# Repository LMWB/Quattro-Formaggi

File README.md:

# DS18B20_OneWire
One Wire Temperature Sensor Breakout Board on Arduino Shield Format and STM32 Nucleo-F446 Based Software

# Features
- four channels 1-Wire Interface with onboard driver stage 
- designed for DS18B20 Temperature Sensor but any 1-Wire Sensor / Actor would do (minor software adjustments required)
- Industrial ready CAN-Bus interface
    - works with standard (11-Bit) and extended (29-Bit) CAN identifier
- Industrial ready Modbus interface will come soon
- Arduino-Shield layout will fit on several Dev-Boards including all Nucleo-64 boards and Arduino-UNO boards

The 1-Wire Search Algorithm and Driver Stage are basically taken from MAXIM Datasheet and Microship App-Notes.

To study some of my testing done so far please have a look [here](/Testing/README.md).

# Quattro Formaggi vs. Quattro Stagioni

# ToDo
- add User-LED on Arduino Shield (Nucleo LED is covered) [HW]
- add Temperature Results to CAN Message [SW]
- use bigger terminal blocks for 1-Wire Interface [HW]
- use bigger terminal blocks for Power Supply and CAN [HW]

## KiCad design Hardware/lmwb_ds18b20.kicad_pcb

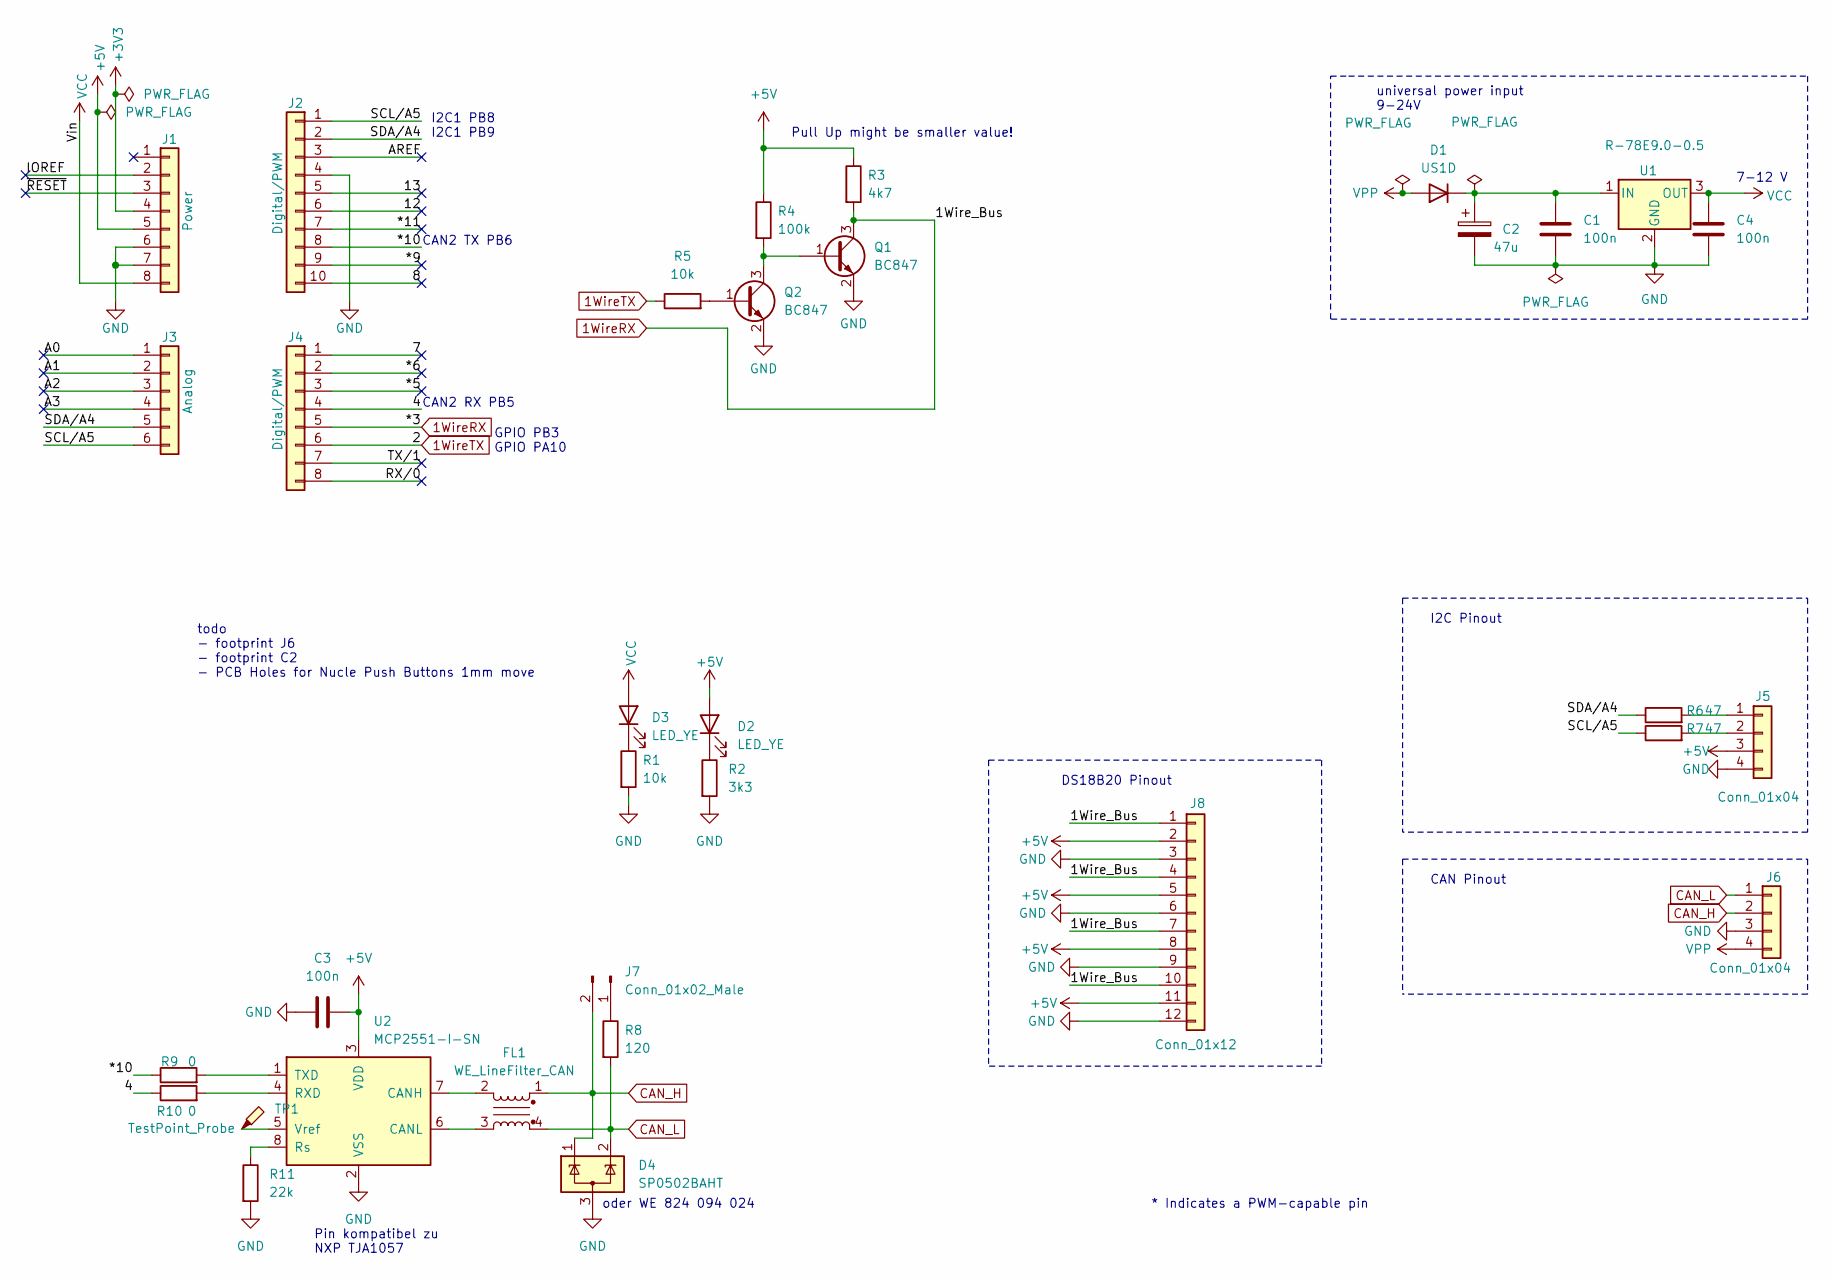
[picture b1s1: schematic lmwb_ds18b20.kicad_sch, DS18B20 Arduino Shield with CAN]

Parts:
C1, C3, C4: 100n; C_1206_3216Metric_Pad1.33x1.80mm_HandSolder
C2: 47u; CP_Elec_10x12.5
D1: US1D; D_SMA
D2, D3: LED_YE; LED_1210_3225Metric_Pad1.42x2.65mm_HandSolder
D4: SP0502BAHT; SOT-23
FL1: WE_LineFilter_CAN; L_CommonModeChoke_CAN_lmwb
J1: Power; PinSocket_1x08_P2.54mm_Vertical
J2: Digital/PWM; PinSocket_1x10_P2.54mm_Vertical
J3: Analog; PinSocket_1x06_P2.54mm_Vertical
J4: Digital/PWM; PinSocket_1x08_P2.54mm_Vertical
J5: Conn_01x04; PinHeader_1x04_P2.54mm_Vertical
J6: Conn_01x04; TerminalBlock_Phoenix_MPT-0,5-4-2.54_1x04_P2.54mm_Horizontal
J7: Conn_01x02_Male; PinHeader_1x02_P2.54mm_Vertical
J8: Conn_01x12; TerminalBlock_Phoenix_MPT-0,5-12-2.54_1x12_P2.54mm_Horizont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
Q1, Q2: BC847; SOT-23
R1, R5: 10k; R_1206_3216Metric_Pad1.30x1.75mm_HandSolder
R2: 3k3; R_1206_3216Metric_Pad1.30x1.75mm_HandSolder
R3: 4k7; R_1206_3216Metric_Pad1.30x1.75mm_HandSolder
R4: 100k; R_1206_3216Metric_Pad1.30x1.75mm_HandSolder
R6, R7: 47; R_1206_3216Metric_Pad1.30x1.75mm_HandSolder
R8: 120; R_1206_3216Metric_Pad1.30x1.75mm_HandSolder
R9, R10: 0; R_1206_3216Metric_Pad1.30x1.75mm_HandSolder
R11: 22k; R_1206_3216Metric_Pad1.30x1.75mm_HandSolder
TP1: TestPoint_Probe; TestPoint_Pad_1.5x1.5mm
U1: R-78E9.0-0.5; Converter_DCDC_RECOM_R-78E-0.5_THT
U2: MCP2551-I-SN; SOIC-8_3.9x4.9mm_P1.27mm

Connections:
1WireRX: J4.5, J8.1, J8.4, J8.7, J8.10, Q1.3 (C), R3.2
1WireTX: J4.6, R5.1
+3V3: J1.4
+5V: C3.2, D2.2 (A), J1.5, J5.3, J8.2, J8.5, J8.8, J8.11, R3.1, R4.1, U2.3 (VDD)
/4: J4.4, R10.1
/7: J4.1
/8: J2.10
/12: J2.6
/13: J2.5
/*5: J4.3
/*6: J4.2
/*9: J2.9
/*10: J2.8, R9.1
/*11: J2.7
/A0: J3.1
/A1: J3.2
/A2: J3.3
/A3: J3.4
/AREF: J2.3
/IOREF: J1.2
/RX/0: J4.8
/SCL/A5: J2.1, J3.6, R7.1
/SDA/A4: J2.2, J3.5, R6.1
/TX/1: J4.7
/~RESET: J1.3
CAN_H: D4.1 (K), FL1.1, J6.2, J7.2
CAN_L: D4.2 (K), FL1.4, J6.1, R8.2
GND: C1.2, C2.2, C3.1, C4.2, D4.3 (A), J1.6, J1.7, J2.4, J5.4, J6.3, J8.3, J8.6, J8.9, J8.12, Q1.2 (E), Q2.2 (E), R1.2, R2.2, R11.2, U1.2 (GND), U2.2 (VSS)
unnamed: C1.1, C2.1, D1.1 (K), U1.1 (IN)
unnamed: D2.1 (K), R2.1
unnamed: D3.1 (K), R1.1
unnamed: FL1.2, U2.7 (CANH)
unnamed: FL1.3, U2.6 (CANL)
unnamed: J5.1, R6.2
unnamed: J5.2, R7.2
unnamed: J7.1, R8.1
unnamed: Q1.1 (B), Q2.3 (C), R4.2
unnamed: Q2.1 (B), R5.2
unnamed: R9.2, U2.1 (TXD)
unnamed: R10.2, U2.4 (RXD)
unnamed: R11.1, U2.8 (Rs)
unnamed: TP1.1, U2.5 (Vref)
VCC: C4.1, D3.2 (A), J1.8, U1.3 (OUT)
VPP: D1.2 (A), J6.4

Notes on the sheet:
Pin kompatibel zu NXP TJA1057
I2C1 PB8 I2C1 PB9
7-12 V
CAN Pinout
CAN2 RX PB5
Pull Up might be smaller value!
GPIO PB3 GPIO PA10
CAN2 TX PB6
todo - footprint J6 - footprint C2 - PCB Holes for Nucle Push Buttons 1mm move
I2C Pinout
oder WE 824 094 024
* Indicates a PWM-capable pin
DS18B20 Pinout
universal power input 9-24V

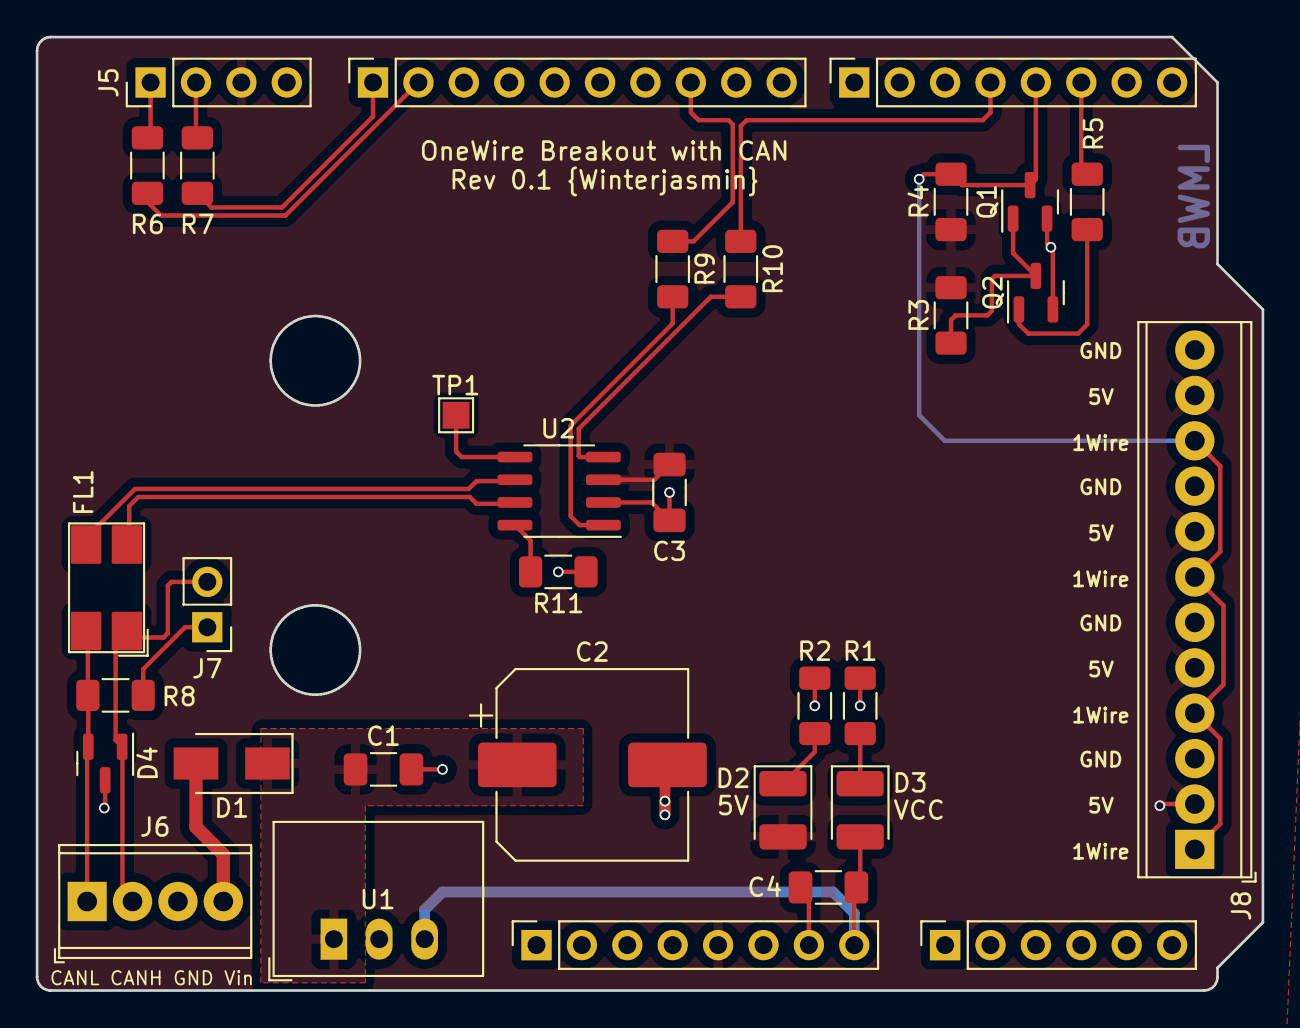
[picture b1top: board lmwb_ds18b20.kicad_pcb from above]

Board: 2 copper layers, 68.6 x 53.3 mm, 33 parts (0 on the bottom side), 26 nets.

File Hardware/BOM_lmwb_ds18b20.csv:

Source:,/home/lukas/KiCad/lmwb_ds18b20/lmwb_ds18b20.kicad_sch,,,,,
Date:,Sat 03 Feb 2024 16:29:55 CET,,,,,
Tool:,Eeschema 6.0.11-2627ca5db0~126~ubuntu22.04.1,,,,,
Generator:,/usr/share/kicad/plugins/bom_csv_grouped_by_value_with_fp.py,,,,,
Component Count:,33,,,,,
,,,,,,
Ref,Qnty,Value,Cmp name,Footprint,Description,Vendor
"C1, C3, C4, ",3,100n,C,Capacitor_SMD:C_1206_3216Metric_Pad1.33x1.80mm_HandSolder,Unpolarized capacitor,
"C2, ",1,47u,C_Polarized,Capacitor_SMD:CP_Elec_10x12.5,Polarized capacitor,
"D1, ",1,US1D,US1D,Diode_SMD:D_SMA,"200V, 1A, General Purpose Rectifier Diode, SMA(DO-214AC)",
"D2, D3, ",2,LED_YE,LED,LED_SMD:LED_1210_3225Metric_Pad1.42x2.65mm_HandSolder,Light emitting diode,
"D4, ",1,SP0502BAHT,SP0502BAHT,Package_TO_SOT_SMD:SOT-23,"TVS Diode Array, 5.5V Standoff, 2 Channels, SOT-23 package",
"FL1, ",1,WE_LineFilter_CAN,WE_LineFilter_CAN,CommonUsedElemetsLMWB:L_CommonModeChoke_CAN_lmwb,"EMI 2-inductor filter, pin-connections 1-4 and 2-3",
"J1, ",1,Power,Conn_01x08,Connector_PinSocket_2.54mm:PinSocket_1x08_P2.54mm_Vertical,"Generic connector, single row, 01x08, script generated (kicad-library-utils/schlib/autogen/connector/)",
"J2, ",1,Digital/PWM,Conn_01x10,Connector_PinSocket_2.54mm:PinSocket_1x10_P2.54mm_Vertical,"Generic connector, single row, 01x10, script generated (kicad-library-utils/schlib/autogen/connector/)",
"J3, ",1,Analog,Conn_01x06,Connector_PinSocket_2.54mm:PinSocket_1x06_P2.54mm_Vertical,"Generic connector, single row, 01x06, script generated (kicad-library-utils/schlib/autogen/connector/)",
"J4, ",1,Digital/PWM,Conn_01x08,Connector_PinSocket_2.54mm:PinSocket_1x08_P2.54mm_Vertical,"Generic connector, single row, 01x08, script generated (kicad-library-utils/schlib/autogen/connector/)",
"J5, ",1,Conn_01x04,Conn_01x04,Connector_PinHeader_2.54mm:PinHeader_1x04_P2.54mm_Vertical,"Generic connector, single row, 01x04, script generated (kicad-library-utils/schlib/autogen/connector/)",
"J6, ",1,Conn_01x04,Conn_01x04,"TerminalBlock_Phoenix:TerminalBlock_Phoenix_MPT-0,5-4-2.54_1x04_P2.54mm_Horizontal","Generic connector, single row, 01x04, script generated (kicad-library-utils/schlib/autogen/connector/)",
"J7, ",1,Conn_01x02_Male,Conn_01x02_Male,Connector_PinHeader_2.54mm:PinHeader_1x02_P2.54mm_Vertical,"Generic connector, single row, 01x02, script generated (kicad-library-utils/schlib/autogen/connector/)",
"J8, ",1,Conn_01x12,Conn_01x12,"TerminalBlock_Phoenix:TerminalBlock_Phoenix_MPT-0,5-12-2.54_1x12_P2.54mm_Horizontal","Generic connector, single row, 01x12, script generated (kicad-library-utils/schlib/autogen/connector/)",
"Q1, Q2, ",2,BC847,BC847,Package_TO_SOT_SMD:SOT-23,"0.1A Ic, 45V Vce, NPN Transistor, SOT-23",
"R1, R5, ",2,10k,R,Resistor_SMD:R_1206_3216Metric_Pad1.30x1.75mm_HandSolder,Resistor,
"R2, ",1,3k3,R,Resistor_SMD:R_1206_3216Metric_Pad1.30x1.75mm_HandSolder,Resistor,
"R3, ",1,4k7,R,Resistor_SMD:R_1206_3216Metric_Pad1.30x1.75mm_HandSolder,Resistor,
"R4, ",1,100k,R,Resistor_SMD:R_1206_3216Metric_Pad1.30x1.75mm_HandSolder,Resistor,
"R6, R7, ",2,47,R,Resistor_SMD:R_1206_3216Metric_Pad1.30x1.75mm_HandSolder,Resistor,
"R8, ",1,120,R,Resistor_SMD:R_1206_3216Metric_Pad1.30x1.75mm_HandSolder,Resistor,
"R9, R10, ",2,0,R,Resistor_SMD:R_1206_3216Metric_Pad1.30x1.75mm_HandSolder,Resistor,
"R11, ",1,22k,R,Resistor_SMD:R_1206_3216Metric_Pad1.30x1.75mm_HandSolder,Resistor,
"TP1, ",1,TestPoint_Probe,TestPoint_Probe,TestPoint:TestPoint_Pad_1.5x1.5mm,test point (alternative probe-style design),
"U1, ",1,R-78E9.0-0.5,R-78E9.0-0.5,Converter_DCDC:Converter_DCDC_RECOM_R-78E-0.5_THT,"500mA Step-Down DC/DC-Regulator, 12-28V input, 9V fixed Output Voltage, LM78xx replacement, -40°C to +85°C, SIP3",
"U2, ",1,MCP2551-I-SN,MCP2551-I-SN,Package_SO:SOIC-8_3.9x4.9mm_P1.27mm,"High-Speed CAN Transceiver, 1Mbps, 5V supply, SOIC-8",

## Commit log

2024-07-15 add software, hardware, datasheet resorces
2024-07-15 pimp readme
2024-07-15 added testing section
2024-07-15 rotate image
2024-07-16 pimp readme add image
2024-07-17 modified readme
2024-07-18 added schematics
2024-09-18 added format csv compatible output string
2024-09-21 added getter for serial-number of one wire diveces present on the bus
2024-09-21 reshape main-loop
2024-09-23 added test results
2025-04-14 Output string format to csv (#1)
    * added format csv compatible output string
    * added getter for serial-number of one wire diveces present on the bus
    * reshape main-loop
    * added test results
    ---------
2025-12-02 get back to work on this branch
2025-12-02 Output string format to csv (#1) (#2)
    * added format csv compatible output string
    * added getter for serial-number of one wire diveces present on the bus
    * reshape main-loop
    * added test results
    ---------
2025-12-02 Output string format to csv (#1) (#2) (#3)
    * added format csv compatible output string
    * added getter for serial-number of one wire diveces present on the bus
    * reshape main-loop
    * added test results
    ---------
2025-12-02 change output string to JSON format
2025-12-03 add new line to output string
